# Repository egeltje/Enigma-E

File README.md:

# Enigma-E

This repository contains snippets of code and designs I create for the Enigma-E kit from the great guys at Cryptomuseum.
For more information, visit https://www.cryptomuseum.com/kits/enigma/

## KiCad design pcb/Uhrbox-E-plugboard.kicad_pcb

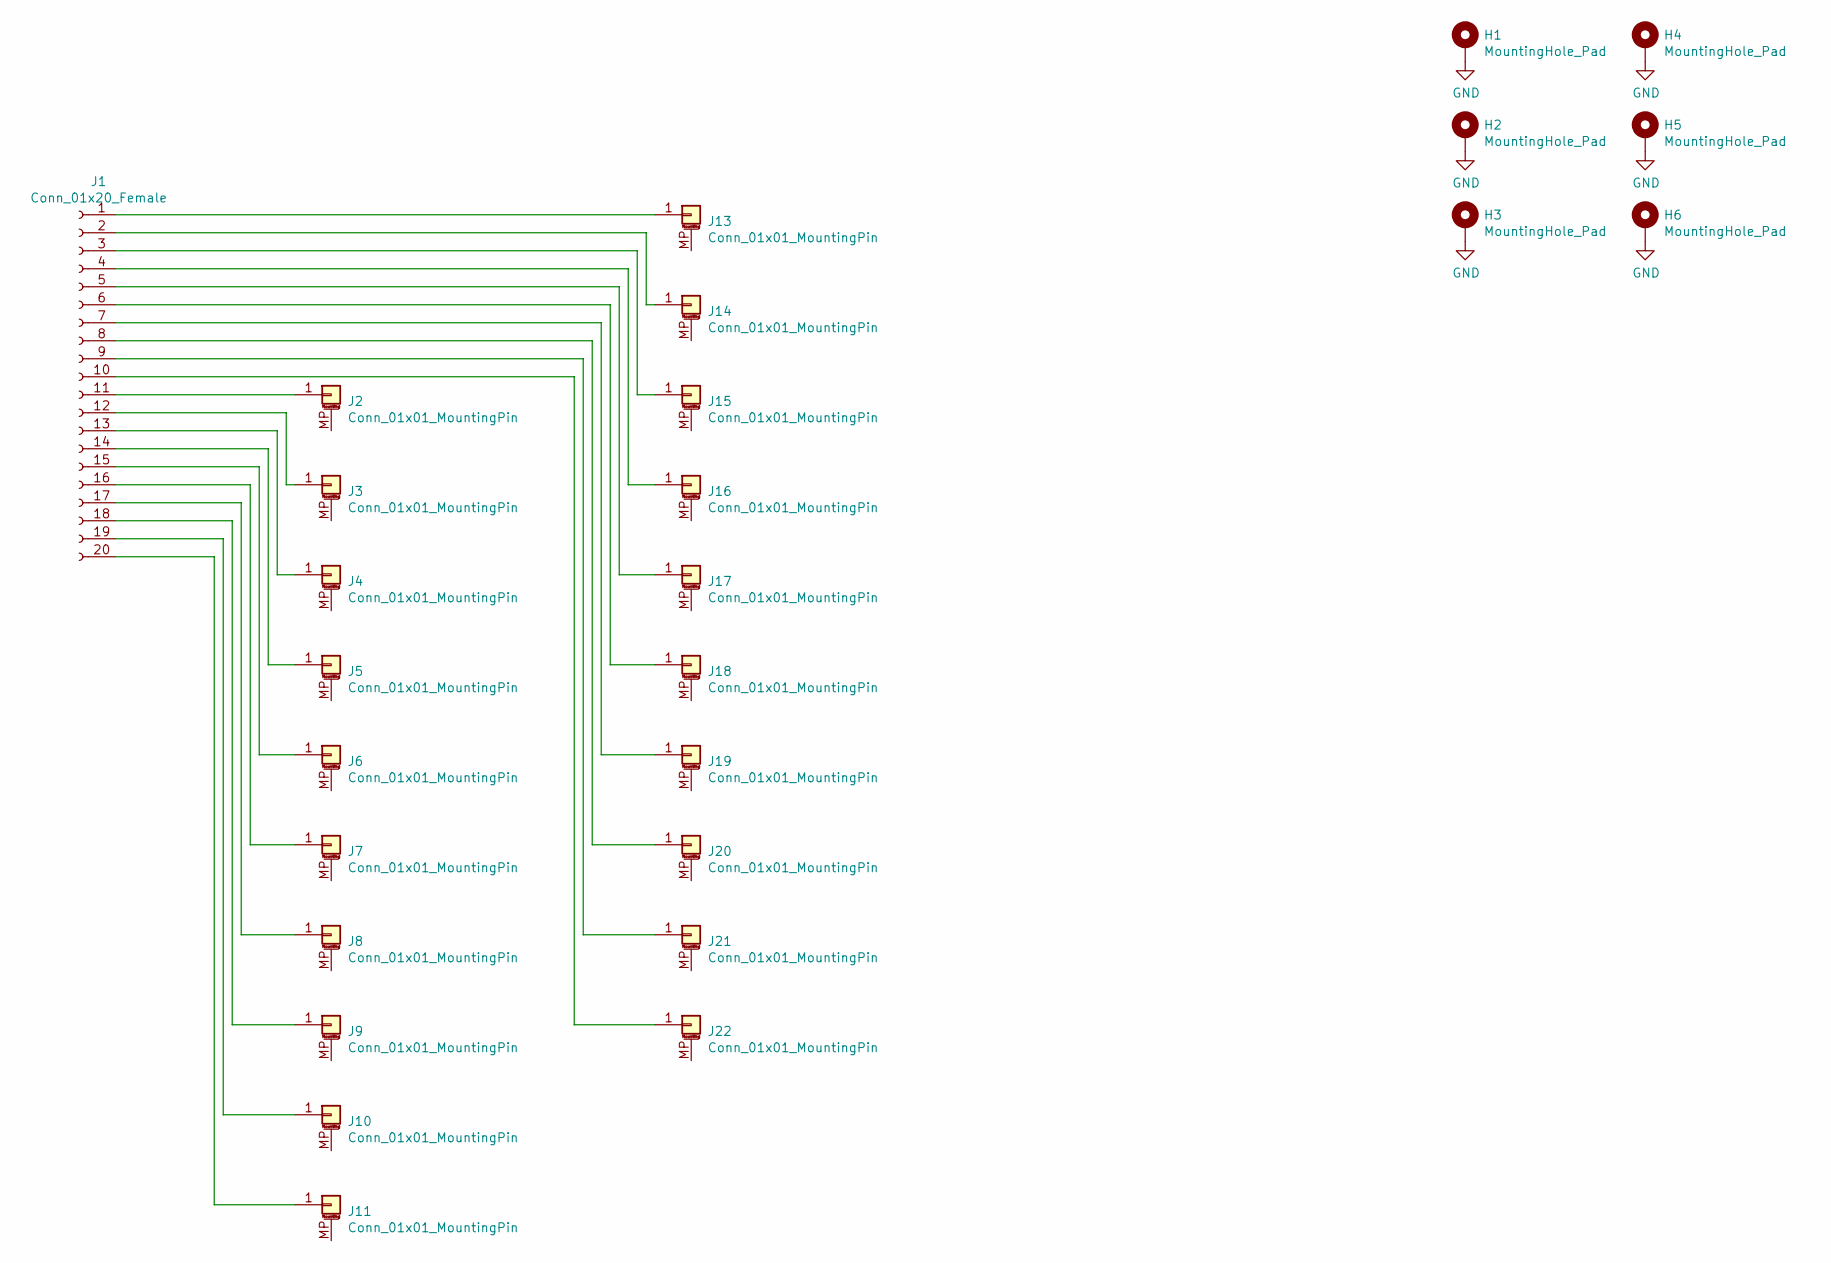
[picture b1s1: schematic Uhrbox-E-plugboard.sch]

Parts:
H1, H2, H3, H4, H5, H6: MountingHole_Pad; MountingHole_3.2mm_M3_Pad
J1: Conn_01x20_Female; PinHeader_1x20_P2.54mm_Vertical
J2, J3, J4, J5, J6, J7, J8, J9, J10, J11, J13, J14, J15, J16, J17, J18, J19, J20, J21, J22: Conn_01x01_MountingPin; Banana_Jack_1Pin_26mm

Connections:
GND: H1.1, H2.1, H3.1, H4.1, H5.1, H6.1
unnamed: J1.1, J13.1
unnamed: J1.2, J14.1
unnamed: J1.3, J15.1
unnamed: J1.4, J16.1
unnamed: J1.5, J17.1
unnamed: J1.6, J18.1
unnamed: J1.7, J19.1
unnamed: J1.8, J20.1
unnamed: J1.9, J21.1
unnamed: J1.10, J22.1
unnamed: J1.11, J2.1
unnamed: J1.12, J3.1
unnamed: J1.13, J4.1
unnamed: J1.14, J5.1
unnamed: J1.15, J6.1
unnamed: J1.16, J7.1
unnamed: J1.17, J8.1
unnamed: J1.18, J9.1
unnamed: J1.19, J10.1
unnamed: J1.20, J11.1

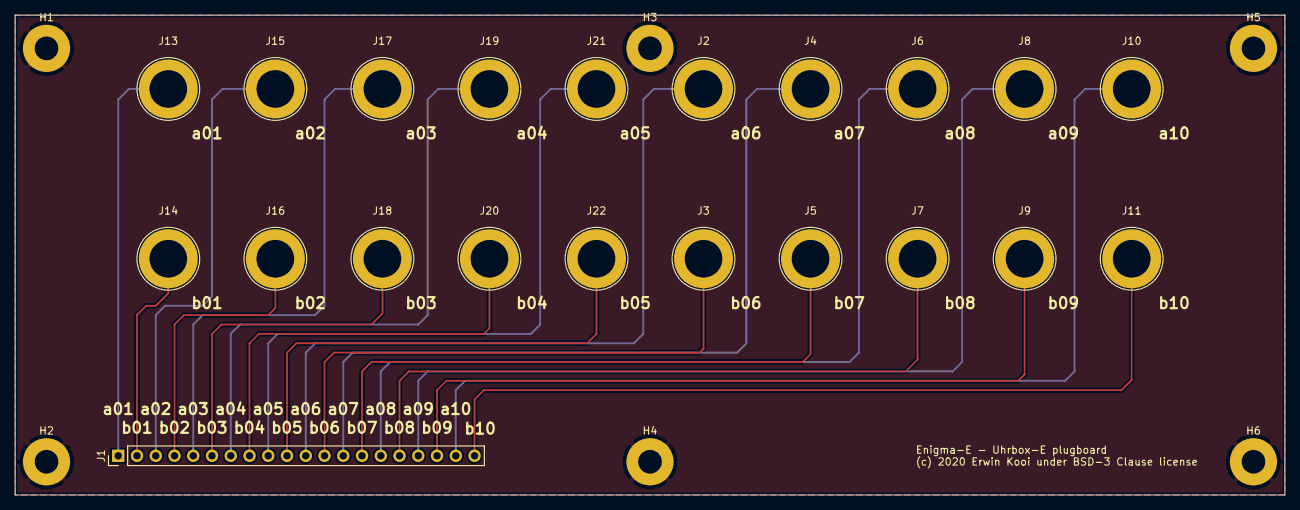
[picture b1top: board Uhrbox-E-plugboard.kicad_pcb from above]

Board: 2 copper layers, 172.0 x 65.0 mm, 27 parts (0 on the bottom side), 21 nets.

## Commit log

2020-07-29 Initial commit.
2020-08-04 Frontpanel and backpanel drawings for cutting/engraving acrylic.
2020-08-05 Modified height of frontpanel and backpanel.
2020-08-07 Added grips and spacers for frontpanel and backpanel.
2020-08-07 Modified screw holes for grips and spacers.
2020-08-28 Added M3 codebook generator
2020-08-28 Added plugboard for Uhrbox-E in backpanel
2020-08-28 Created PCB for Uhrbox-E plugboard
2020-08-28 Added KiCAD backup files to gitignore
2020-08-29 Add screw for stability to Uhrbox-E plugboard
2020-08-29 Removed non-existing A reflector
2020-09-01 Changed ascii characters to ord()
2020-09-21 Uhrbord-E plugboard PCB sent to manufacturing
2020-09-30 Changed header to 2.54mm and sent to manufacturing
2020-09-30 Changed serial connector on frontpanel
2020-10-01 Minor adjustments to front panel

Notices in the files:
pcb/Uhrbox-E-plugboard.kicad_pcb:
(c) 2020 Erwin Kooi under BSD-3 Clause license
